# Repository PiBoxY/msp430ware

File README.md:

# TI MSP430Ware Mirror
Quicken your development time with MSP430Ware, a tool for navigating the available resources that support MSP430 and MSP432 devices. Using this GUI or clicking through the folder tree to the left, we offer code examples, software libraries, datasheets and other resources - all at the tip of your fingers.

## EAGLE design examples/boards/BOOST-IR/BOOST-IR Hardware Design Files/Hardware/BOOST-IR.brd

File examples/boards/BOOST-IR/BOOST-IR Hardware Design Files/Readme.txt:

BOOST-IR Hardware Design Files v1.00.00
Texas Instruments, Inc.

********************************************************************************
Welcome to the BOOST-IR BoosterPack!
********************************************************************************

In this package, you will find hardware design files that can help you quickly
get started on developing your own project.

Available in the 'Hardware' folder are the complete board schematic and layout,
bill of material, and Gerber files.

For more resources, be sure to visit www.ti.com/tool/boost-ir

********************************************************************************
Revision History
********************************************************************************
Ver 1.00.00 - December 10th, 2014
- Initial Release

********************************************************************************
Project File Listing
********************************************************************************
|--Documentation                      : Folder containing links to more resources
|--Hardware                           : Folder containing board design files, bill of material, gerber
|--Readme.txt                         : This file

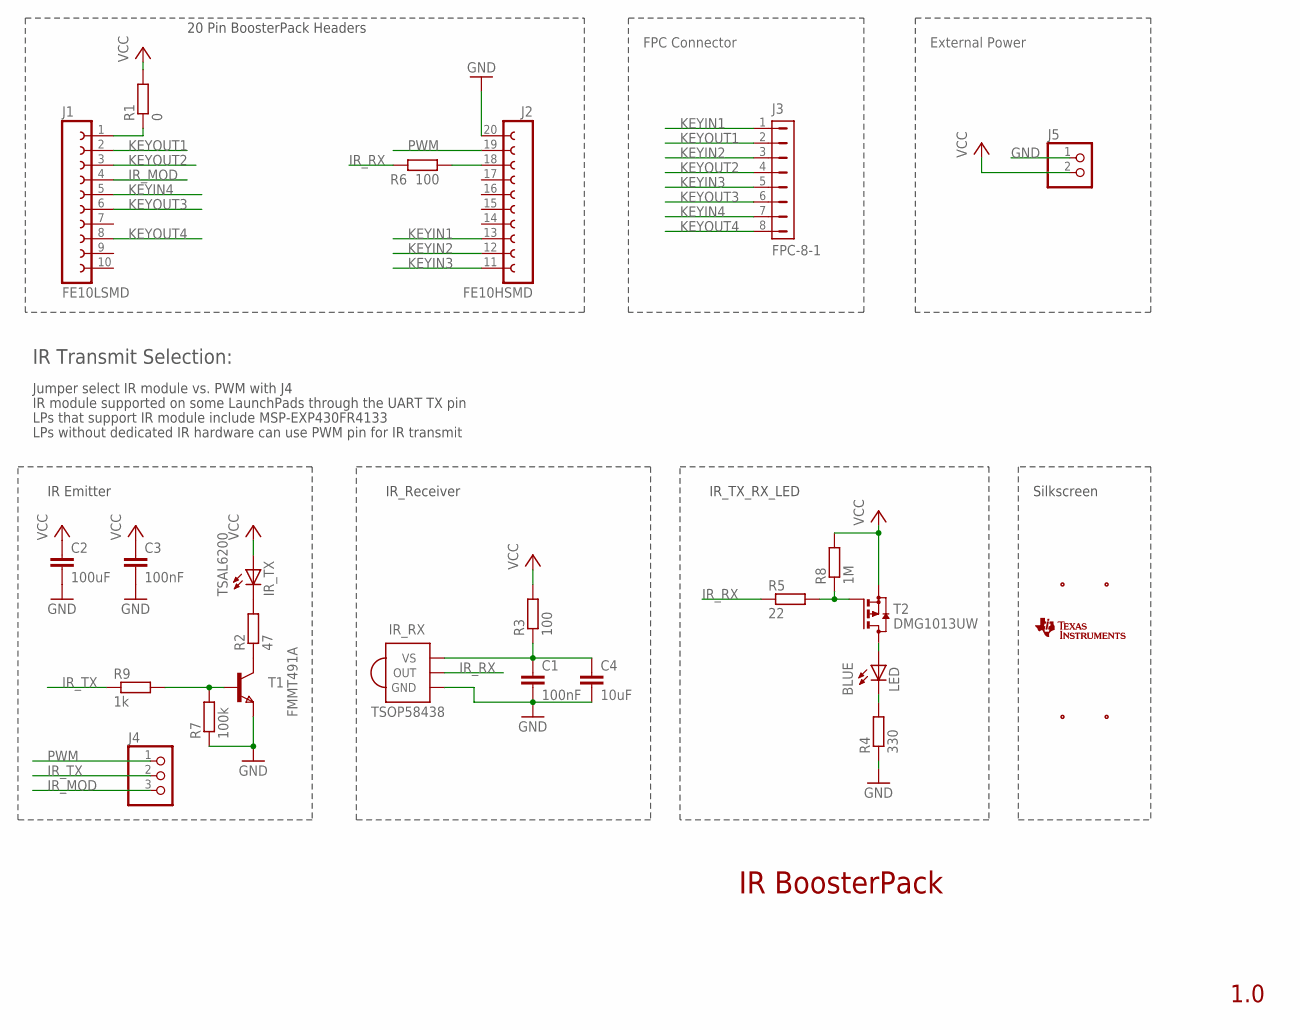
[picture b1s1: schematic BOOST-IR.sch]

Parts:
C1, C3: 100nF; C0603
C2: 100uF; C1206
C4: 10uF; C0805
IR_RX: TSOP58438
IR_TX: TSAL6200; IR_LED_PAC
J1: FE10LSMD; FE10SMD
J2: FE10HSMD
J3: FPC-8-1; FPC_IR
J4: PINHD1X3; 1X03
J5: HEADER1X2
LED: BLUE; CHIPLED_0603
R1: 0; R1206
R2: 47; R1206
R3, R6: 100; R0603
R4: 330; R0603
R5: 22; R0603
R7: 100k; R0603
R8: 1M; R0603
R9: 1k; R0603
T1: FMMT491A; SOT-23
T2: DMG1013UW; SOT323
U$1: BOOST-IR_EXTPOWER
U$3: TI_LOGO_LETTERS; TI_LOGO_WORDS
U$4: BOOST-IR_LABEL
U$5: BOOST-IR_REV0.1LOGO; BOOST-IR_LOGO
U$6: BOOST-IR_REV0.1LOGOSMALL; BOOST-IR_LOGOSMALL

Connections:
GND: C1.2, C2.2, C3.2, C4.2, IR_RX.GND, J2.20 (10), J5.1, R4.1, R7.1, T1.2 (E)
IR_MOD: J1.4 (7), J4.3
IR_RX: IR_RX.OUT, R5.1, R6.1
IR_TX: J4.2, R9.1
KEYIN1: J2.13 (3), J3.1
KEYIN2: J2.12 (2), J3.3
KEYIN3: J2.11 (1), J3.5
KEYIN4: J1.5 (6), J3.7
KEYOUT1: J1.2 (9), J3.2
KEYOUT2: J1.3 (8), J3.4
KEYOUT3: J1.6 (5), J3.6
KEYOUT4: J1.8 (3), J3.8
unnamed: R2.1, T1.1 (C)
unnamed: IR_TX.K (C), R2.2
unnamed: R7.2, R9.2, T1.3 (B)
unnamed: C1.1, C4.1, IR_RX.VS, R3.1
unnamed: R5.2, R8.1, T2.1 (G)
unnamed: LED.A, T2.3 (D)
unnamed: LED.C, R4.2
unnamed: J2.18 (8), R6.2
unnamed: J1.1 (10), R1.1
PWM: J2.19 (9), J4.1
VCC: C2.1, C3.1, IR_TX.A, J5.2, R1.2, R3.2, R8.2, T2.2 (S)

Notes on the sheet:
IR BoosterPack
20 Pin BoosterPack Headers
IR Emitter
FPC Connector
IR_Receiver
IR_TX_RX_LED
1.0
Silkscreen
IR Transmit Selection:
Jumper select IR module vs. PWM with J4
LPs that support IR module include MSP-EXP430FR4133
IR module supported on some LaunchPads through the UART TX pin
LPs without dedicated IR hardware can use PWM pin for IR transmit
External Power

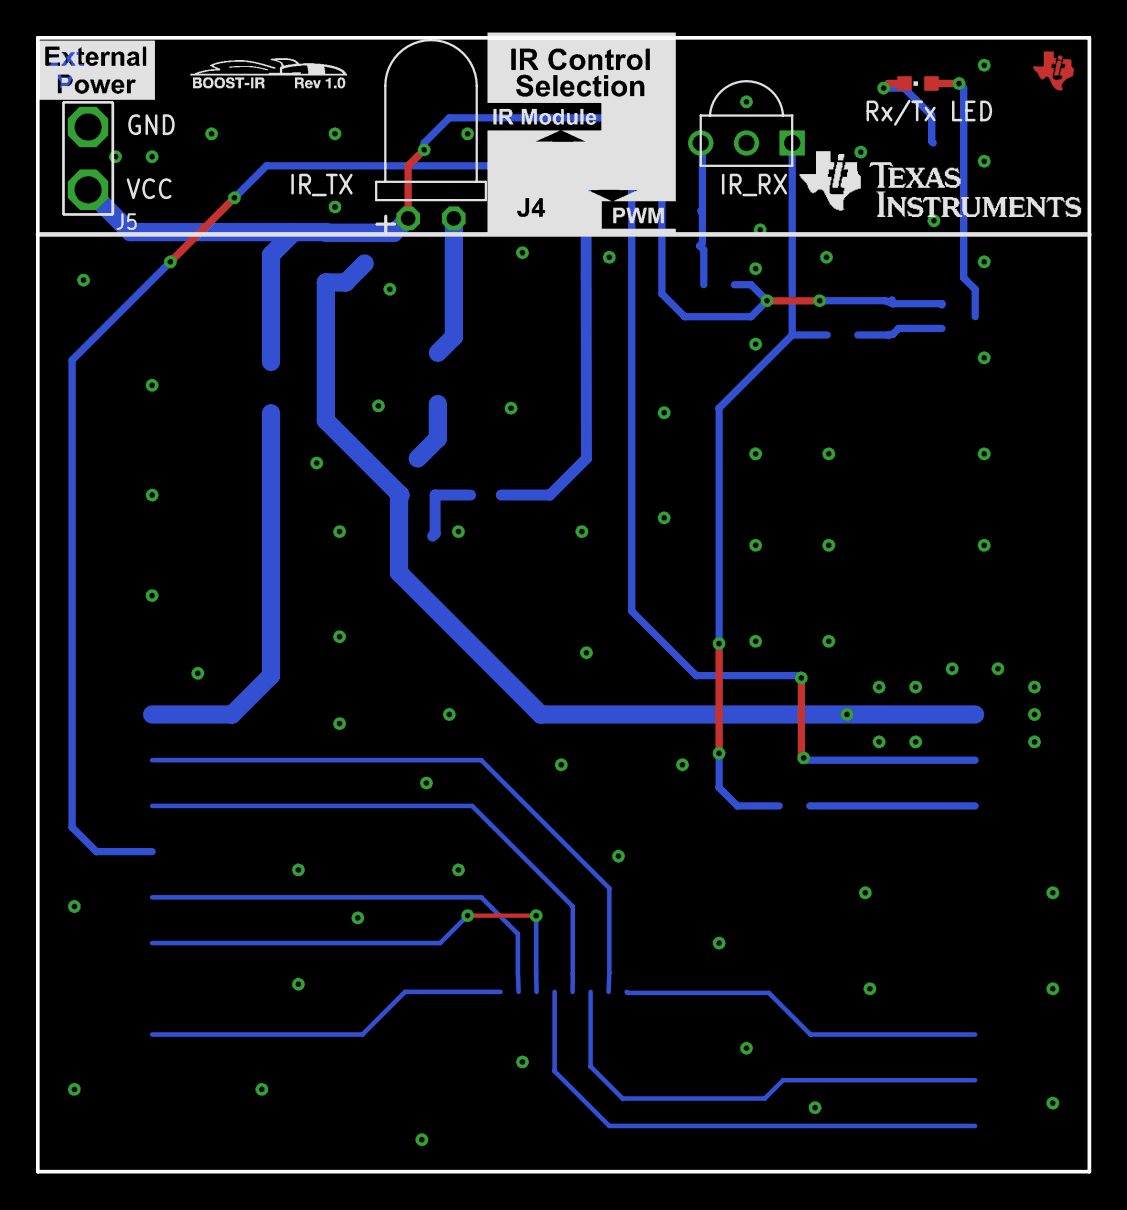
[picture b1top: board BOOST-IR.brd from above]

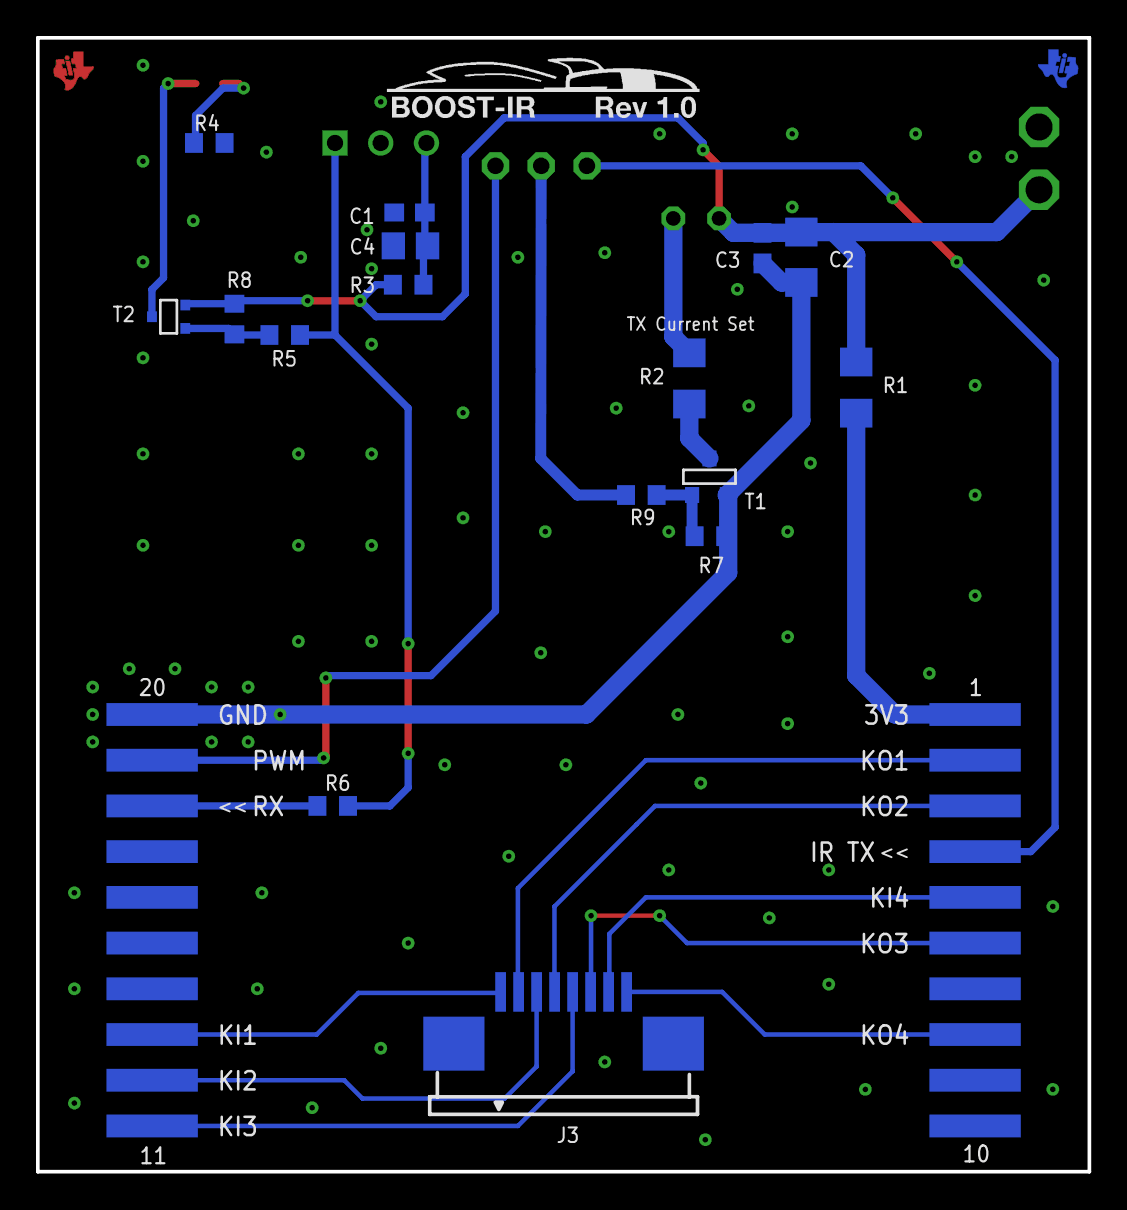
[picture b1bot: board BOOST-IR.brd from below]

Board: 4 copper layers, 58.4 x 63.0 mm, 30 parts (19 on the bottom side), 23 nets.

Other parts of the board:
U$2, U$7: TILOGO_SMALL

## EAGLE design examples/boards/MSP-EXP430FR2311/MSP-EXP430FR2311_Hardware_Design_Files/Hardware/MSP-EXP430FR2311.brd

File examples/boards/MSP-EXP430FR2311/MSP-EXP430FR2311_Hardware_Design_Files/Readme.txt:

MSP-EXP430FR2311 Software Examples v1.00.01
Texas Instruments, Inc.

********************************************************************************
Welcome to the MSP-EXP430FR2311 LaunchPad!
********************************************************************************

In this package, you will find hardware design files that can help you quickly
get started on developing your own project.

Available in the 'Hardware' folder are the complete board schematic and layout,
bill of material and Gerber files.

You can also find various web links in the 'Documentation' folder pointing to
the Tool Page, Quick Start Guide, and User's Guide.

For more resources, be sure to visit www.ti.com/tool/msp-exp430fr6989

********************************************************************************
Revision History
********************************************************************************
Ver 1.00.01 - June 3rd, 2016
- Minor update to project settings

Ver 1.00.00 - Feb 17th, 2016
- Initial Release

********************************************************************************
Project File Listing
********************************************************************************
|--Documentation                      : Folder containing links to more resources
|--Hardware                           : Folder containing hardware design files,
                                        bill of material and gerber files
|--Readme.txt                         : This file

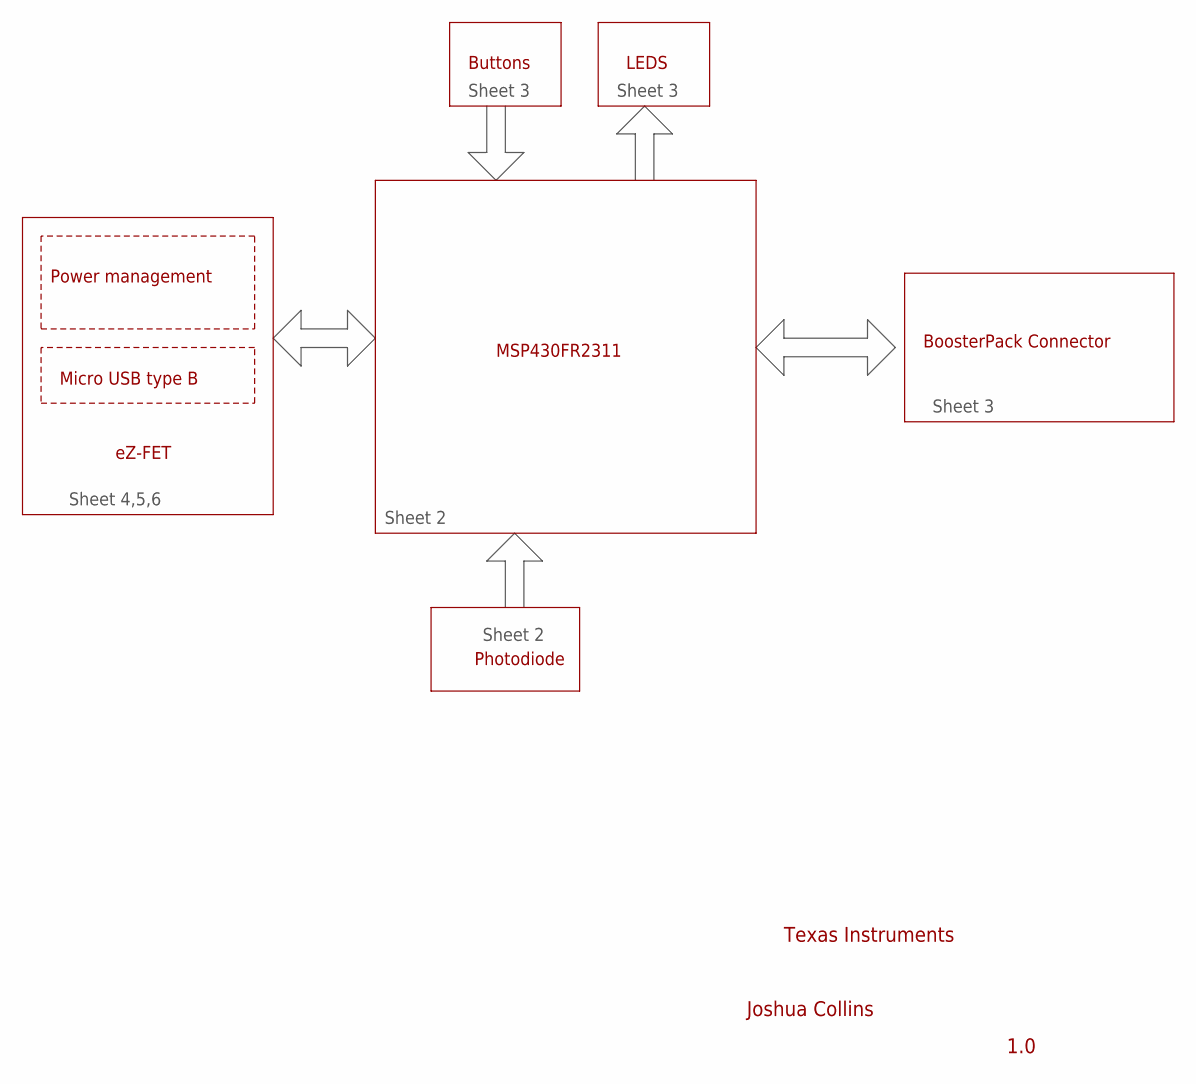
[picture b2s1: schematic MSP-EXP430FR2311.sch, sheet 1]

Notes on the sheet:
Power management
Micro USB type B
eZ-FET
MSP430FR2311
BoosterPack Connector
LEDS
Buttons
Sheet 2
Sheet 4,5,6
Sheet 3
Texas Instruments
Joshua Collins
Photodiode

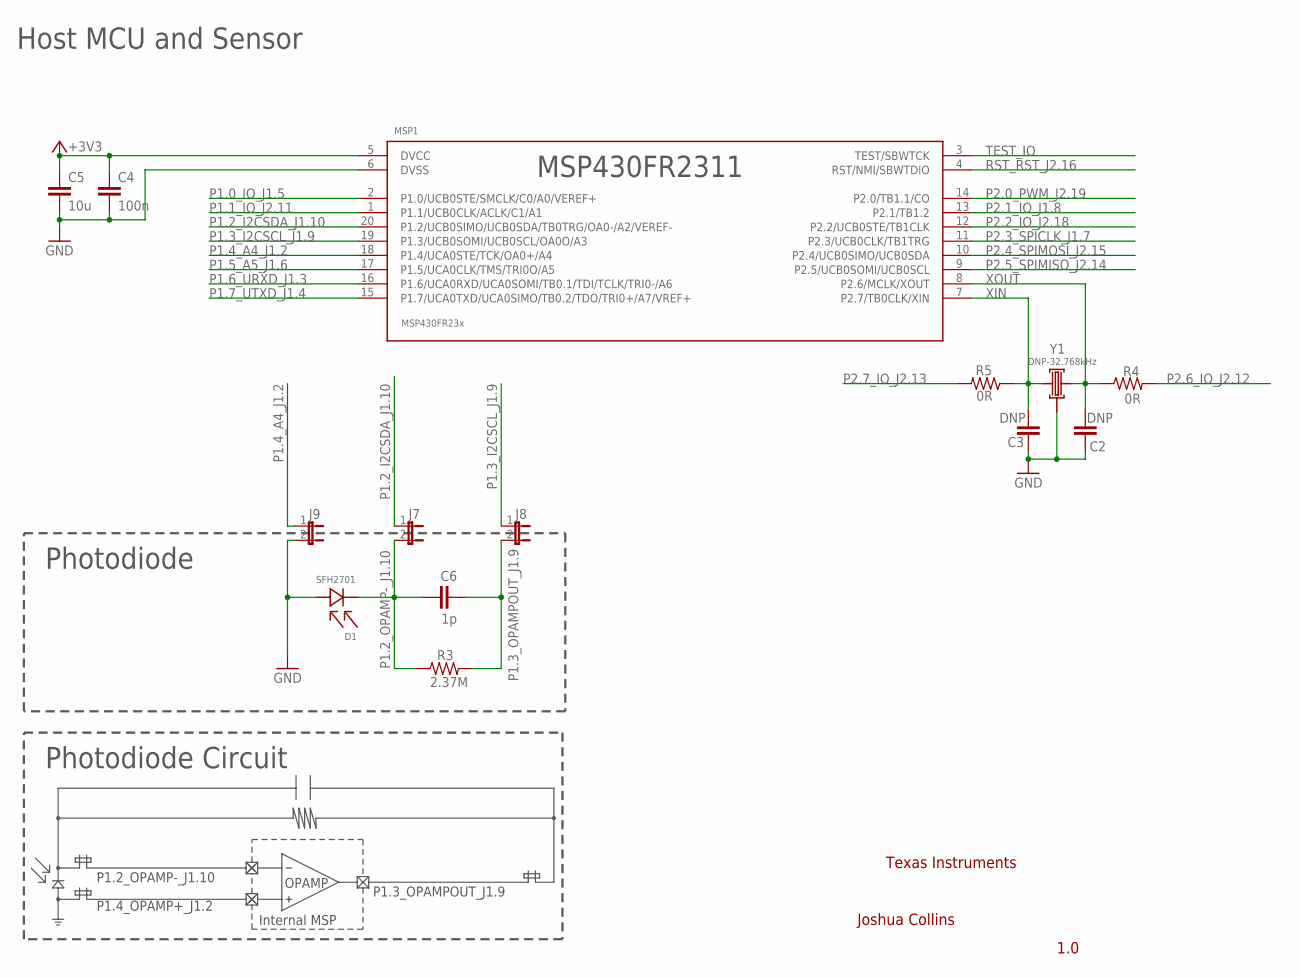
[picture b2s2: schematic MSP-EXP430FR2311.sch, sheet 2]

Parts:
C2, C3: DNP; 0402
C4: 100n; 0402
C5: 10u; C0603
C6: 1p; C0603
D1: SFH2701; 1206-OSRAM
J7, J8, J9: JUMPER-2.54
MSP1: MSP430FR2311IPW20"; PW20
R3: 2.37M; 0603
R4, R5: 0R; 0402
Y1: DNP - 32.768kHz; MULTI-CRYSTAL

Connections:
+3V3: C4.1, C5.1, MSP1.5 (DVCC); also elsewhere on the board
P1.0_IO_J1.5: MSP1.2 (P1.0/UCB0STE/SMCLK/C0/A0/VEREF+); also elsewhere on the board
P1.1_IO_J2.11: MSP1.1 (P1.1/UCB0CLK/ACLK/C1/A1); also elsewhere on the board
P1.2_I2CSDA_J1.10: J7.1, MSP1.20 (P1.2/UCB0SIMO/UCB0SDA/TB0TRG/OA0-/A2/VE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); also elsewhere on the board
P1.2_OPAMP-_J1.10: C6.1, D1.C, J7.2, R3.1
P1.3_I2CSCL_J1.9: J8.1, MSP1.19 (P1.3/UCB0SOMI/UCB0SCL/OA0O/A3); also elsewhere on the board
P1.3_OPAMPOUT_J1.9: C6.2, J8.2, R3.2
P1.4_A4_J1.2: J9.1, MSP1.18 (P1.4/UCA0STE/TCK/OA0+/A4); also elsewhere on the board
P1.5_A5_J1.6: MSP1.17 (P1.5/UCA0CLK/TMS/TRI0O/A5); also elsewhere on the board
P1.6_URXD_J1.3: MSP1.16 (P1.6/UCA0RXD/UCA0SOMI/TB0.1/TDI/TCLK/TR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); also elsewhere on the board
P1.7_UTXD_J1.4: MSP1.15 (P1.7/UCA0TXD/UCA0SIMO/TB0.2/TDO/TRI0+/A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); also elsewhere on the board
P2.0_PWM_J2.19: MSP1.14 (P2.0/TB1.1/CO); also elsewhere on the board
P2.1_IO_J1.8: MSP1.13 (P2.1/TB1.2); also elsewhere on the board
P2.2_IO_J2.18: MSP1.12 (P2.2/UCB0STE/TB1CLK); also elsewhere on the board
P2.3_SPICLK_J1.7: MSP1.11 (P2.3/UCB0CLK/TB1TRG); also elsewhere on the board
P2.4_SPIMOSI_J2.15: MSP1.10 (P2.4/UCB0SIMO/UCB0SDA); also elsewhere on the board
P2.5_SPIMISO_J2.14: MSP1.9 (P2.5/UCB0SOMI/UCB0SCL); also elsewhere on the board
P2.6_IO_J2.12: R4.2; also elsewhere on the board
P2.7_IO_J2.13: R5.2; also elsewhere on the board
RST_RST_J2.16: MSP1.4 (RST/NMI/SBWTDIO); also elsewhere on the board
TEST_IO: MSP1.3 (TEST/SBWTCK); also elsewhere on the board
TGT_GND: C2.2, C3.2, C4.2, C5.2, D1.A, J9.2, MSP1.6 (DVSS), Y1.GND@0 (GND); also elsewhere on the board
XIN: C3.1, MSP1.7 (P2.7/TB0CLK/XIN), R5.1, Y1.1
XOUT: C2.1, MSP1.8 (P2.6/MCLK/XOUT), R4.1, Y1.2

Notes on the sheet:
Host MCU and Sensor
MSP430FR2311
Texas Instruments
Joshua Collins
Photodiode
Photodiode Circuit
OPAMP
Internal MSP
P1.3_OPAMPOUT_J1.9
P1.2_OPAMP-_J1.10
P1.4_OPAMP+_J1.2
DNP-32.768kHz

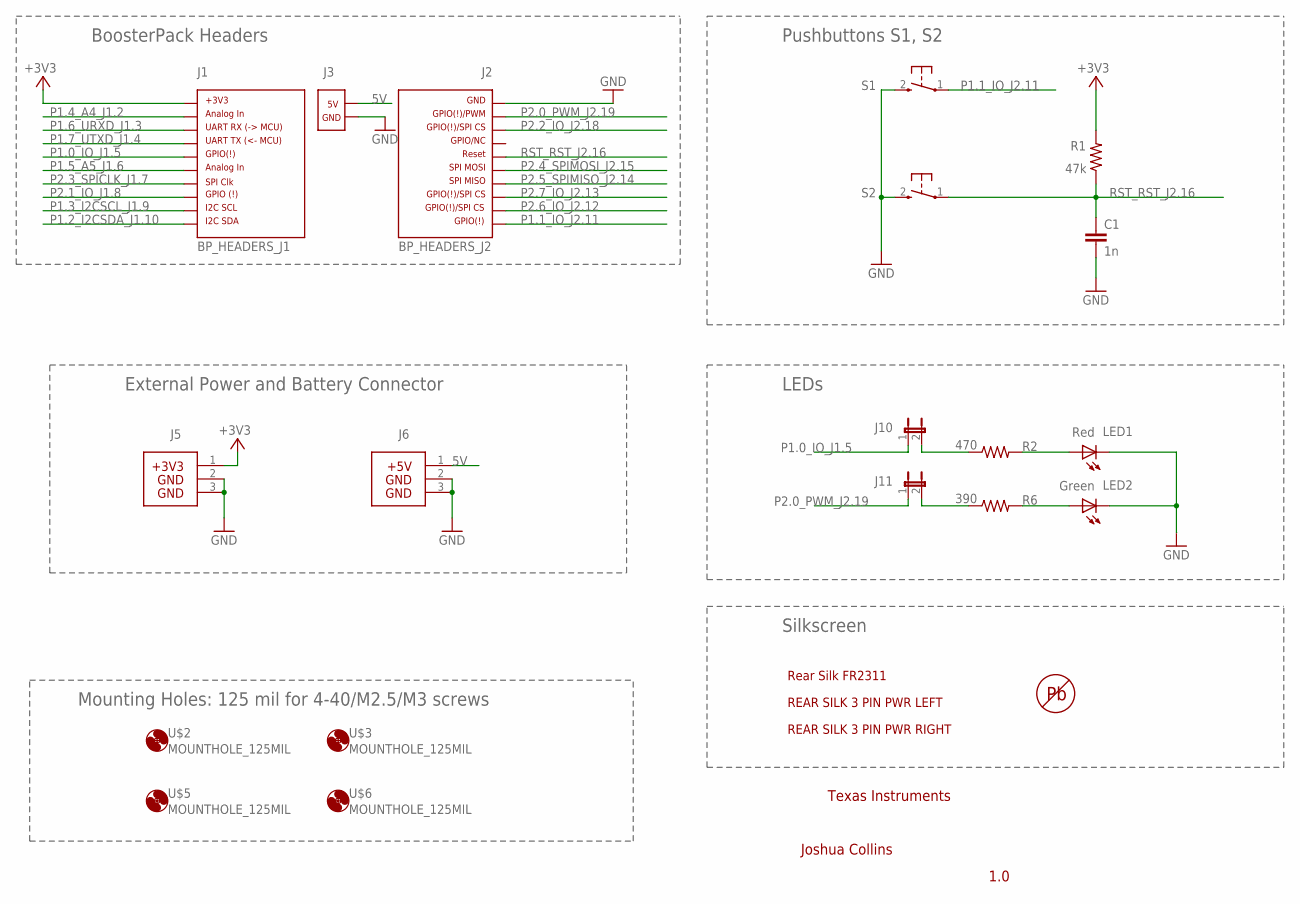
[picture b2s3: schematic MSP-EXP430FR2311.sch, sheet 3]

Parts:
C1: 1n; 0402
J1: BP_HEADERS_J1; J1
J2: BP_HEADERS_J2; J2
J3: BP_2PIN_J3_HEADER; 2PIN_PWR_5V
J5: HEADER 1X03; 3PIN_PWR_3V3
J6: BP_HEADERS_PWR_5V; 3PIN_PWR_5V
J10, J11: JUMPER-2.54
LED1: Red; LED0805
LED2: Green; LED0805
R1: 47k; 0402
R2: 470; 0402
R6: 390; 0402
S1, S2: PB; PBTH
U$1: REAR_SILK_FR2311; SILK_REAR_FR2311
U$2, U$3, U$5, U$6: MOUNTHOLE_125MIL
U$7: PB-FREE
U$8: BP_3PIN_SILK; 3PIN_PWR_SILK
U$9: P
U$10: BP_3PIN_SILK_RT; 3PIN_PWR_SILK_RT

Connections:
5V: J3.21, J6.1; also elsewhere on the board
+3V3: J1.1, J5.1, R1.2; also elsewhere on the board
unnamed: J11.2, R6.1
unnamed: LED2.A, R6.2
unnamed: J10.2, R2.1
unnamed: LED1.A, R2.2
P1.0_IO_J1.5: J1.5, J10.1; also elsewhere on the board
P1.1_IO_J2.11: J2.11, S1.1; also elsewhere on the board
P1.2_I2CSDA_J1.10: J1.10; also elsewhere on the board
P1.3_I2CSCL_J1.9: J1.9; also elsewhere on the board
P1.4_A4_J1.2: J1.2; also elsewhere on the board
P1.5_A5_J1.6: J1.6; also elsewhere on the board
P1.6_URXD_J1.3: J1.3; also elsewhere on the board
P1.7_UTXD_J1.4: J1.4; also elsewhere on the board
P2.0_PWM_J2.19: J2.19, J11.1; also elsewhere on the board
P2.1_IO_J1.8: J1.8; also elsewhere on the board
P2.2_IO_J2.18: J2.18; also elsewhere on the board
P2.3_SPICLK_J1.7: J1.7; also elsewhere on the board
P2.4_SPIMOSI_J2.15: J2.15; also elsewhere on the board
P2.5_SPIMISO_J2.14: J2.14; also elsewhere on the board
P2.6_IO_J2.12: J2.12; also elsewhere on the board
P2.7_IO_J2.13: J2.13; also elsewhere on the board
RST_RST_J2.16: C1.1, J2.16, R1.1, S2.1; also elsewhere on the board
TGT_GND: C1.2, J2.20, J3.22, J5.2, J5.3, J6.2, J6.3, LED1.C, LED2.C, S1.2 (S), S2.2 (S); also elsewhere on the board

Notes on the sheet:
Mounting Holes: 125 mil for 4-40/M2.5/M3 screws
BoosterPack Headers
Pushbuttons S1, S2
External Power and Battery Connector
LEDs
Silkscreen
Texas Instruments
Joshua Collins

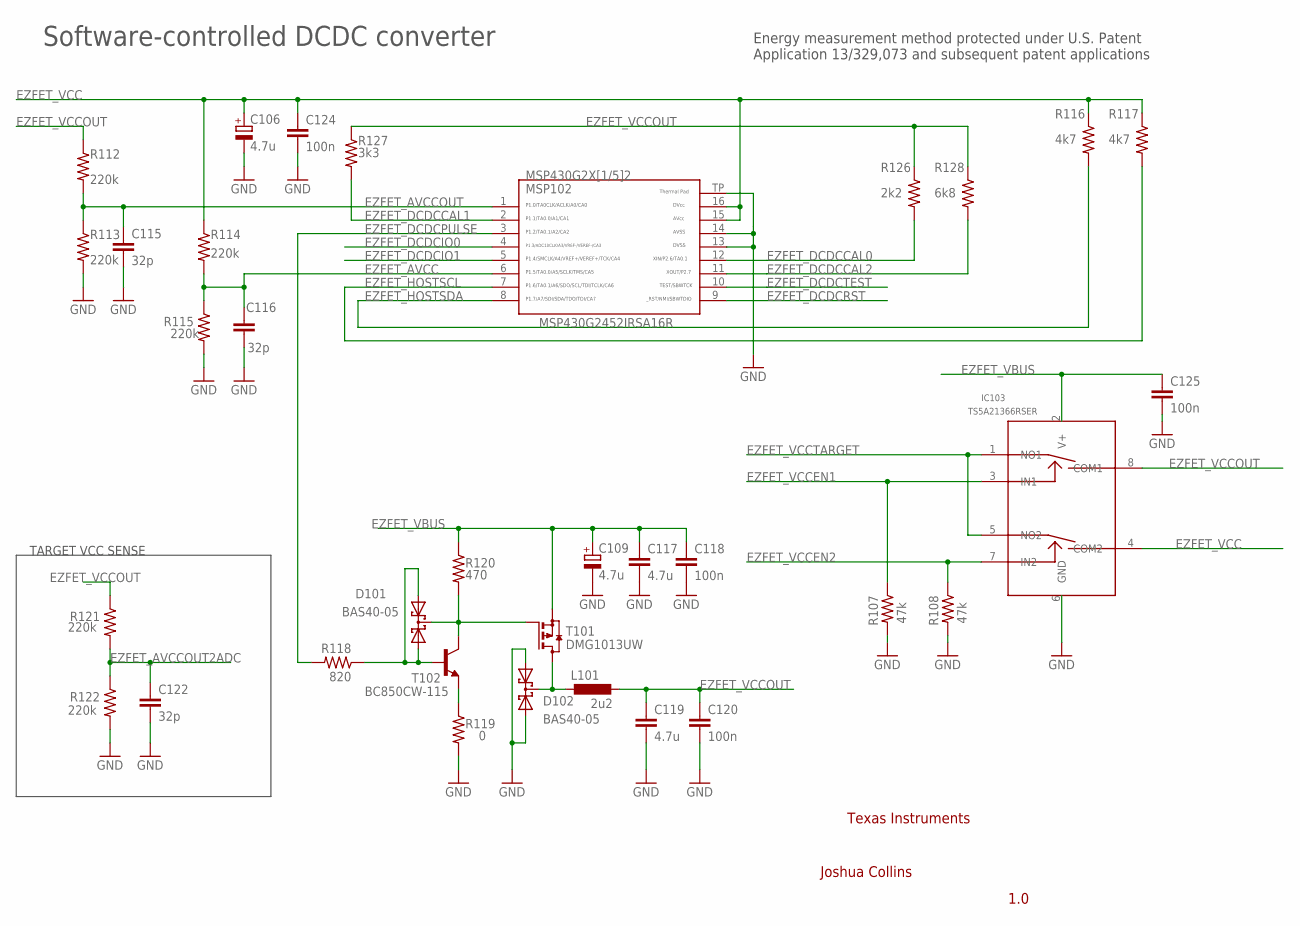
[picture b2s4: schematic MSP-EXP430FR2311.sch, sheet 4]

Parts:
C106, C109: 4.7u; A/3216-18R
C115, C116, C122: 32p; 0402
C117, C119: 4.7u; C0603
C118, C120, C124, C125: 100n; 0402
D101, D102: BAS40-05; SOT323
IC103: TS5A21366RSER; UQFN_RSE
L101: 2u2; L3216C
MSP102: MSP430G2452IRSA16R; RSA16
R107, R108: 47k; 0402
R112, R113, R114, R115, R121, R122: 220k; 0402
R116, R117: 4k7; 0402
R118: 820; 0402
R119: 0; 0402
R120: 470; 0402
R126: 2k2; 0402
R127: 3k3; 0402
R128: 6k8; 0402
T101: DMG1013UW; SOT323
T102: BC850CW-115; SOT323

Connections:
EZFET_AVCC: C116.2, MSP102.6, R114.2, R115.1
EZFET_AVCCOUT: C115.2, MSP102.1, R112.2, R113.1
EZFET_AVCCOUT2ADC: C122.2, R121.2, R122.1; also elsewhere on the board
EZFET_DCDCCAL0: MSP102.12, R126.2
EZFET_DCDCCAL1: MSP102.2, R127.2
EZFET_DCDCCAL2: MSP102.11, R128.2
EZFET_DCDCIO0: MSP102.4; also elsewhere on the board
EZFET_DCDCIO1: MSP102.5; also elsewhere on the board
EZFET_DCDCPULSE: MSP102.3, R118.2; also elsewhere on the board
EZFET_DCDCRST: MSP102.9; also elsewhere on the board
EZFET_DCDCTEST: MSP102.10; also elsewhere on the board
EZFET_HOSTSCL: MSP102.7, R117.2; also elsewhere on the board
EZFET_HOSTSDA: MSP102.8, R116.2; also elsewhere on the board
EZFET_VBUS: C109.+, C117.1, C118.1, C125.1, IC103.2 (V+), R120.1, T101.2 (S); also elsewhere on the board
EZFET_VCC: C106.+, C124.1, IC103.4 (COM2), MSP102.15, MSP102.16, R114.1, R116.1, R117.1; also elsewhere on the board
EZFET_VCCEN1: IC103.3 (IN1), R107.1; also elsewhere on the board
EZFET_VCCEN2: IC103.7 (IN2), R108.1; also elsewhere on the board
EZFET_VCCOUT: C119.1, C120.1, IC103.8 (COM1), L101.2, R112.1, R121.1, R126.1, R127.1, R128.1
EZFET_VCCTARGET: IC103.1 (NO1), IC103.5 (NO2); also elsewhere on the board
GND: C106.-, C109.-, C115.1, C116.1, C117.2, C118.2, C119.2, C120.2, C122.1, C124.2, C125.2, D102.1 (A1), D102.2 (A2), IC103.6 (GND), MSP102.13, MSP102.14, MSP102.TP, R107.2, R108.2, R113.2, R115.2, R119.2, R122.2; also elsewhere on the board
unnamed: R119.1, T102.2 (E)
unnamed: D101.1 (A1), D101.2 (A2), R118.1, T102.1 (B)
unnamed: D102.3 (C), L101.1, T101.3 (D)
unnamed: D101.3 (C), R120.2, T101.1 (G), T102.3 (C)

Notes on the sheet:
Software-controlled DCDC converter
TARGET VCC SENSE
MSP430G2452IRSA16R
Texas Instruments
Joshua Collins
Energy measurement method protected under U.S. Patent Application 13/329,073 and subsequent patent applications

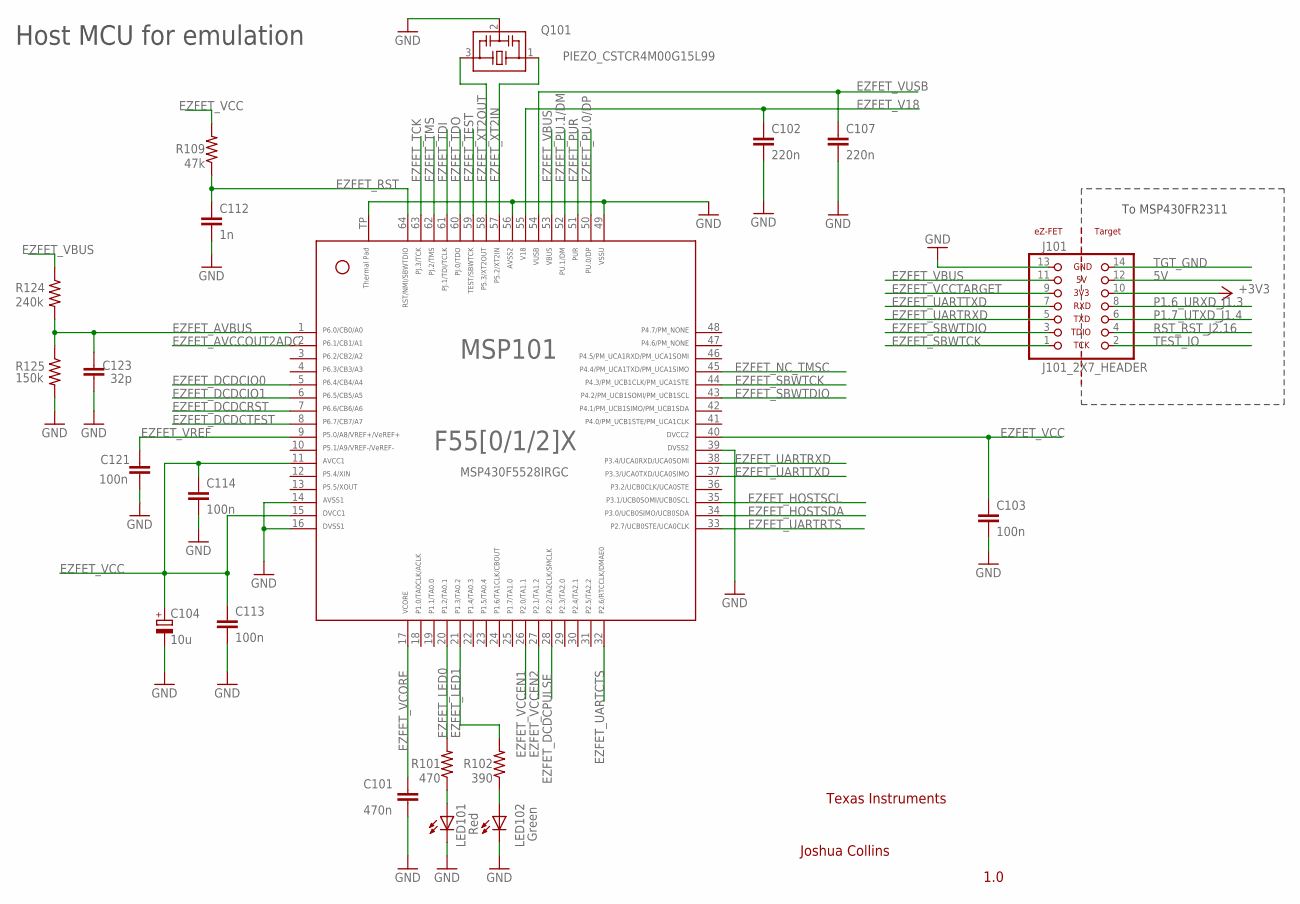
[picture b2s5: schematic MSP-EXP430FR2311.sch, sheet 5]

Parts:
C101: 470n; 0402
C102, C107: 220n; 0402
C103, C113, C114, C121: 100n; 0402
C104: 10u; A/3216-18R
C112: 1n; 0402
C123: 32p; 0402
J101: J101_2X7_HEADER; J101
LED101: Red; LED0805
LED102: Green; LED0805
MSP101: MSP430F5528IRGC; RGC64
Q101: PIEZO_CSTCR4M00G15L99; CSTCR4M
R101: 470; 0402
R102: 390; 0402
R109: 47k; 0402
R124: 240k; 0402
R125: 150k; 0402

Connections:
5V: J101.12; also elsewhere on the board
+3V3: J101.10; also elsewhere on the board
EZFET_AVBUS: C123.2, MSP101.1, R124.2, R125.1
EZFET_AVCCOUT2ADC: MSP101.2; also elsewhere on the board
EZFET_DCDCIO0: MSP101.5; also elsewhere on the board
EZFET_DCDCIO1: MSP101.6; also elsewhere on the board
EZFET_DCDCPULSE: MSP101.28; also elsewhere on the board
EZFET_DCDCRST: MSP101.7; also elsewhere on the board
EZFET_DCDCTEST: MSP101.8; also elsewhere on the board
EZFET_HOSTSCL: MSP101.35; also elsewhere on the board
EZFET_HOSTSDA: MSP101.34; also elsewhere on the board
EZFET_LED0: MSP101.20, R101.2
EZFET_LED1: MSP101.21, R102.2
EZFET_NC_TMSC: MSP101.45
EZFET_PU.0/DP: MSP101.50; also elsewhere on the board
EZFET_PU.1/DM: MSP101.52; also elsewhere on the board
EZFET_PUR: MSP101.51; also elsewhere on the board
EZFET_RST: C112.1, MSP101.64, R109.1; also elsewhere on the board
EZFET_SBWTCK: J101.1, MSP101.44
EZFET_SBWTDIO: J101.3, MSP101.43
EZFET_TCK: MSP101.63; also elsewhere on the board
EZFET_TDI: MSP101.61; also elsewhere on the board
EZFET_TDO: MSP101.60; also elsewhere on the board
EZFET_TEST: MSP101.59; also elsewhere on the board
EZFET_TMS: MSP101.62; also elsewhere on the board
EZFET_UARTCTS: MSP101.32
EZFET_UARTRTS: MSP101.33
EZFET_UARTRXD: J101.5, MSP101.38
EZFET_UARTTXD: J101.7, MSP101.37
EZFET_V18: C102.1, MSP101.55
EZFET_VBUS: J101.11, MSP101.53, R124.1; also elsewhere on the board
EZFET_VCC: C103.1, C104.+, C113.1, C114.1, MSP101.11, MSP101.15, MSP101.40, R109.2; also elsewhere on the board
EZFET_VCCEN1: MSP101.26; also elsewhere on the board
EZFET_VCCEN2: MSP101.27; also elsewhere on the board
EZFET_VCCTARGET: J101.9; also elsewhere on the board
EZFET_VCORE: C101.1, MSP101.17
EZFET_VREF: C121.1, MSP101.9
EZFET_VUSB: C107.1, MSP101.54
EZFET_XT2IN: MSP101.57, Q101.1
EZFET_XT2OUT: MSP101.58, Q101.3
GND: C101.2, C102.2, C103.2, C104.-, C107.2, C112.2, C113.2, C114.2, C121.2, C123.1, J101.13, LED101.C, LED102.C, MSP101.14, MSP101.16, MSP101.39, MSP101.49, MSP101.56, MSP101.TP, Q101.2, R125.2; also elsewhere on the board
unnamed: LED101.A, R101.1
unnamed: LED102.A, R102.1
P1.6_URXD_J1.3: J101.8; also elsewhere on the board
P1.7_UTXD_J1.4: J101.6; also elsewhere on the board
RST_RST_J2.16: J101.4; also elsewhere on the board
TEST_IO: J101.2; also elsewhere on the board
TGT_GND: J101.14; also elsewhere on the board

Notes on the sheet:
Host MCU for emulation
MSP430F5528IRGC
To MSP430FR2311
Texas Instruments
Joshua Collins

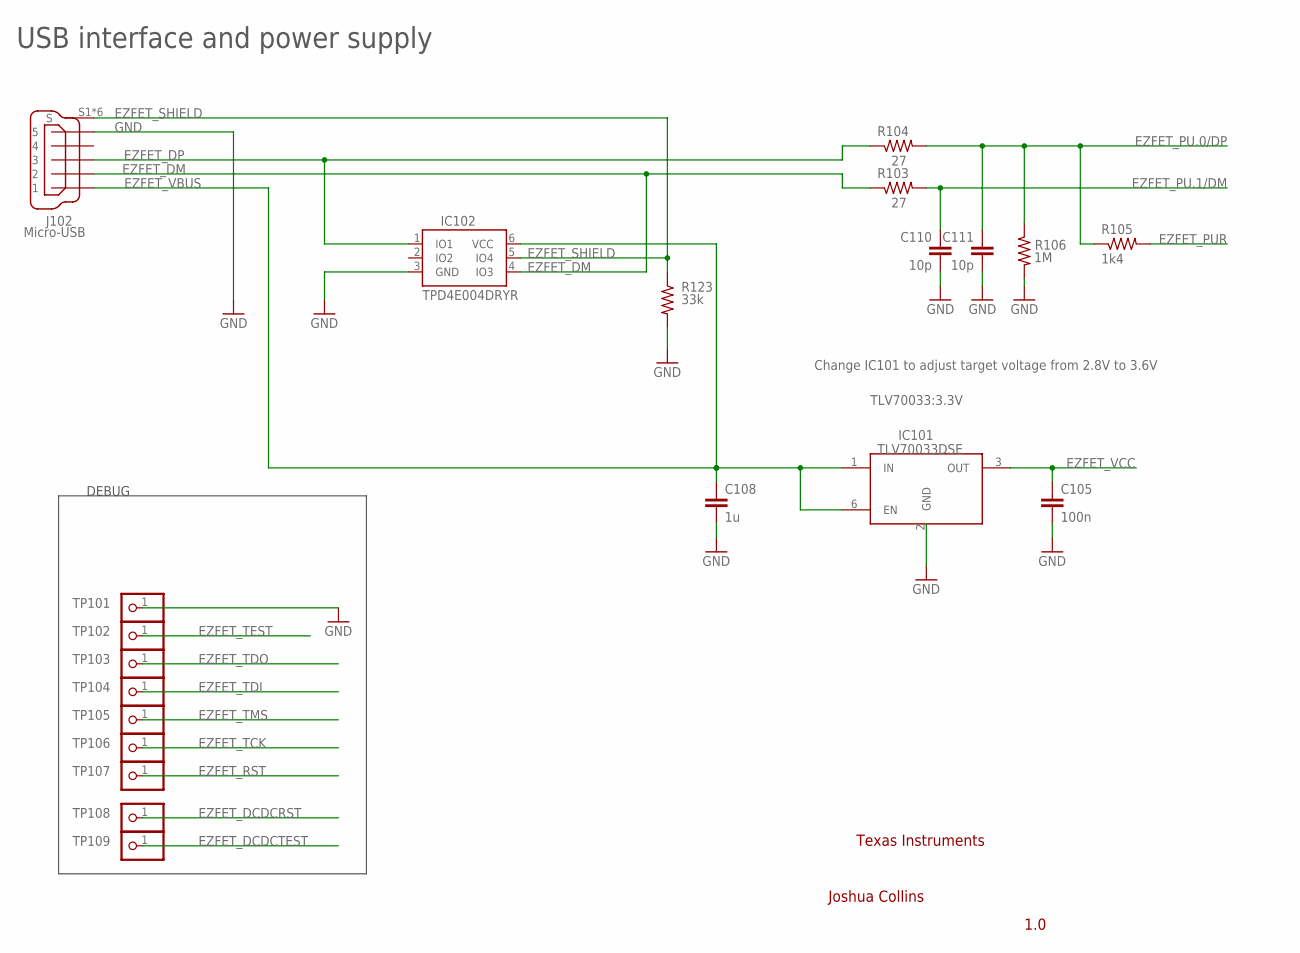
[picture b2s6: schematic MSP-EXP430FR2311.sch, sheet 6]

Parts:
C105: 100n; 0402
C108: 1u; C0603
C110, C111: 10p; 0402
IC101: TLV70033DSE; WSON_DSE
IC102: TPD4E004DRYR; SON(DRY)6
J102: Micro-USB; EZFET_UX62M-B-5P
R103, R104: 27; 0402
R105: 1k4; 0402
R106: 1M; 0402
R123: 33k; 0402
TP101, TP102, TP103, TP104, TP105, TP106, TP107, TP108, TP109: TEST_PIN2; 1X01

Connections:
EZFET_DCDCRST: TP108.1; also elsewhere on the board
EZFET_DCDCTEST: TP109.1; also elsewhere on the board
EZFET_DM: IC102.4 (IO3), J102.2, R103.1
EZFET_DP: IC102.1 (IO1), J102.3, R104.1
EZFET_PU.0/DP: C111.1, R104.2, R105.1, R106.1; also elsewhere on the board
EZFET_PU.1/DM: C110.1, R103.2; also elsewhere on the board
EZFET_PUR: R105.2; also elsewhere on the board
EZFET_RST: TP107.1; also elsewhere on the board
EZFET_SHIELD: IC102.5 (IO4), J102.S1 (S), J102.S2 (S), J102.S3 (S), J102.S4 (S), J102.S5 (S), J102.S6 (S), R123.1
EZFET_TCK: TP106.1; also elsewhere on the board
EZFET_TDI: TP104.1; also elsewhere on the board
EZFET_TDO: TP103.1; also elsewhere on the board
EZFET_TEST: TP102.1; also elsewhere on the board
EZFET_TMS: TP105.1; also elsewhere on the board
EZFET_VBUS: C108.1, IC101.1 (IN), IC101.6 (EN), IC102.6 (VCC), J102.1; also elsewhere on the board
EZFET_VCC: C105.1, IC101.3 (OUT); also elsewhere on the board
GND: C105.2, C108.2, C110.2, C111.2, IC101.2 (GND), IC102.3 (GND), J102.5, R106.2, R123.2, TP101.1; also elsewhere on the board

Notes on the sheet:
USB interface and power supply
DEBUG
Change IC101 to adjust target voltage from 2.8V to 3.6V
TLV70033:3.3V
TLV70033DSE
Texas Instruments
Joshua Collins

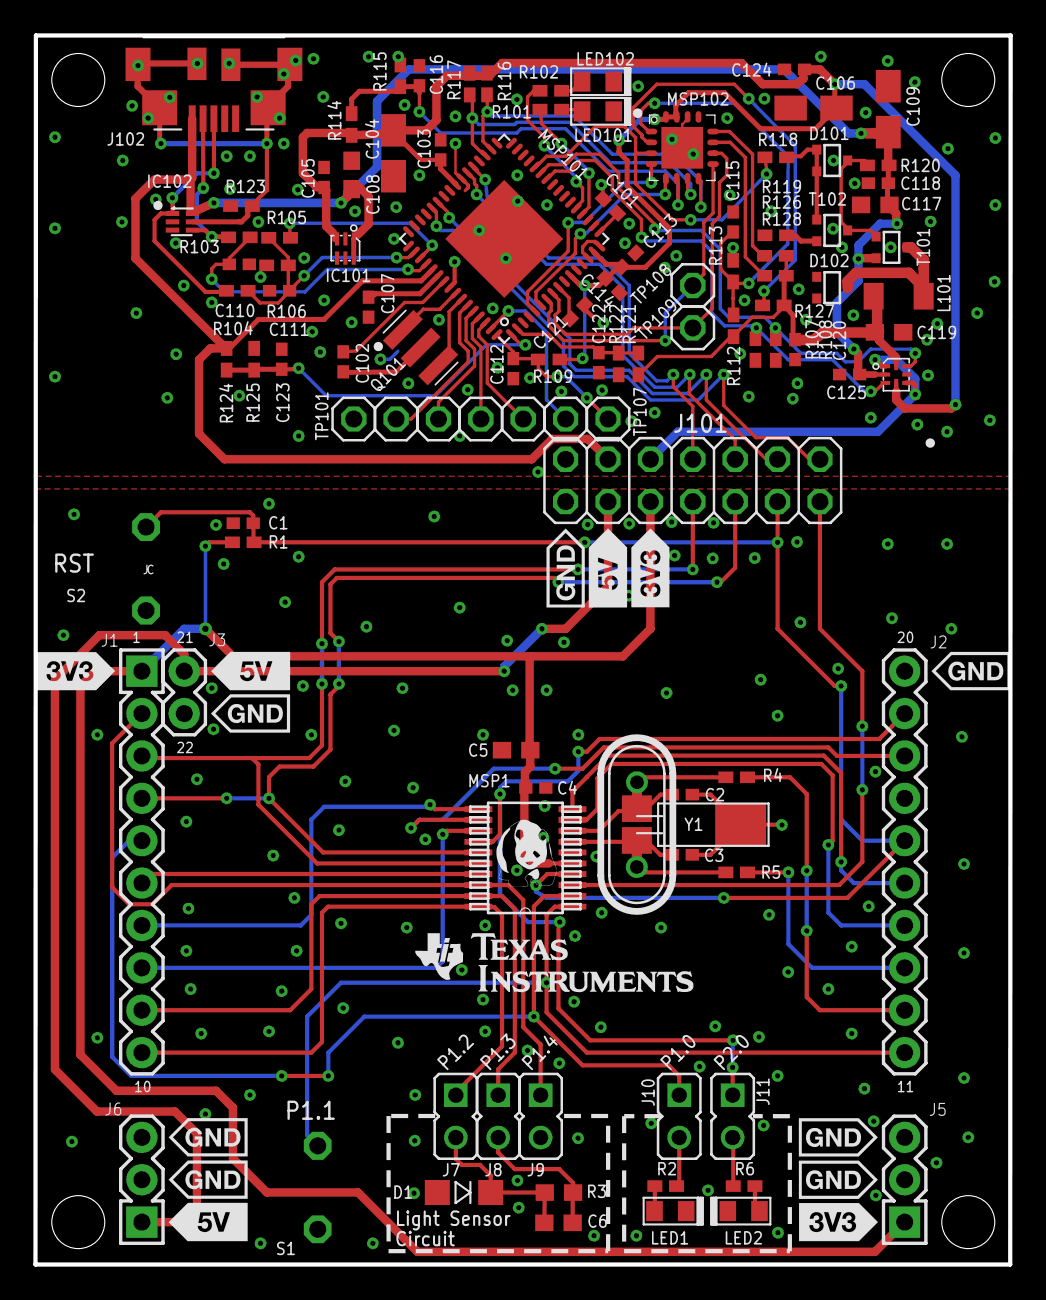
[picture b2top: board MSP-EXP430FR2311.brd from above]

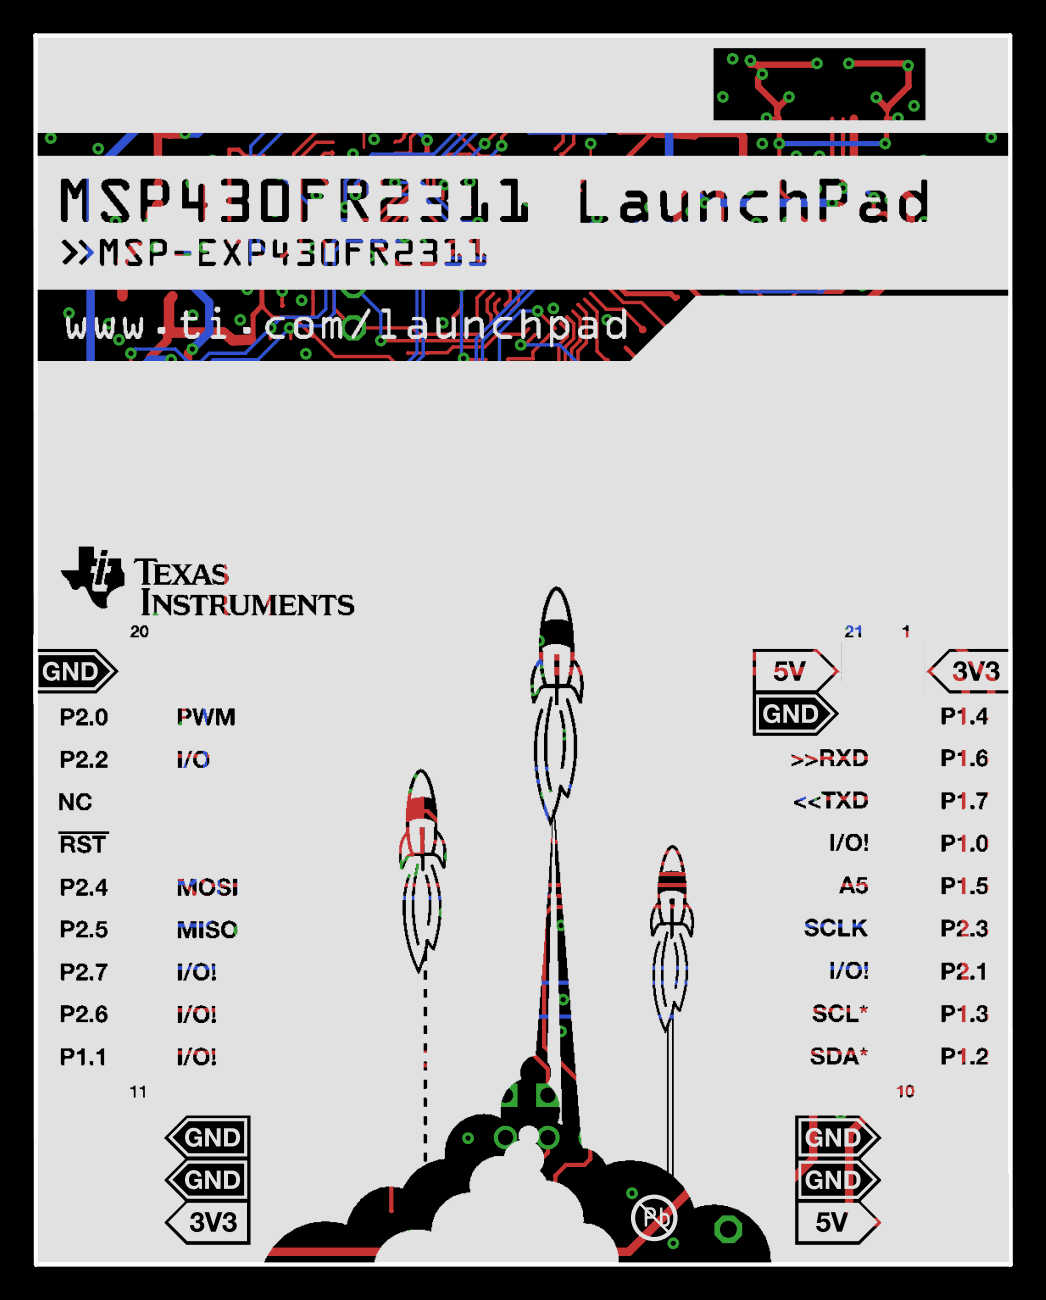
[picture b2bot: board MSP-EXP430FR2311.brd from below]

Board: 2 copper layers, 58.4 x 73.7 mm, 116 parts (2 on the bottom side), 80 nets.

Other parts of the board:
DRAW1, DRAW3: LOGO-ROCKET-10X7MM-BRD
U$4: LOGO16_TPLACE

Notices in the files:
examples/boards/BOOST-IR/BOOST-IR Hardware Design Files/Hardware/BOOST-IR.brd:
(C)2003 A. DANNENBERG
parts and their libraries:
TI-LaunchPad-Eagle: As far as I know the LaunchPad rocket is released by TI under the Creative Commons license.
